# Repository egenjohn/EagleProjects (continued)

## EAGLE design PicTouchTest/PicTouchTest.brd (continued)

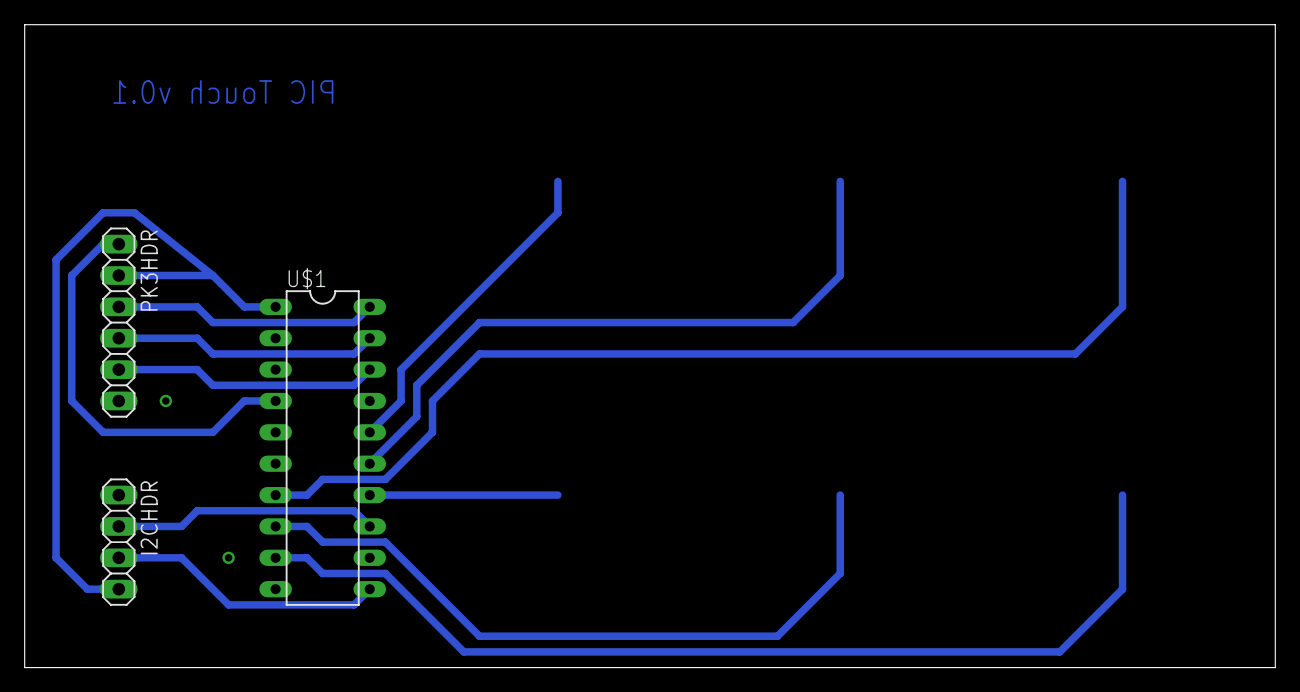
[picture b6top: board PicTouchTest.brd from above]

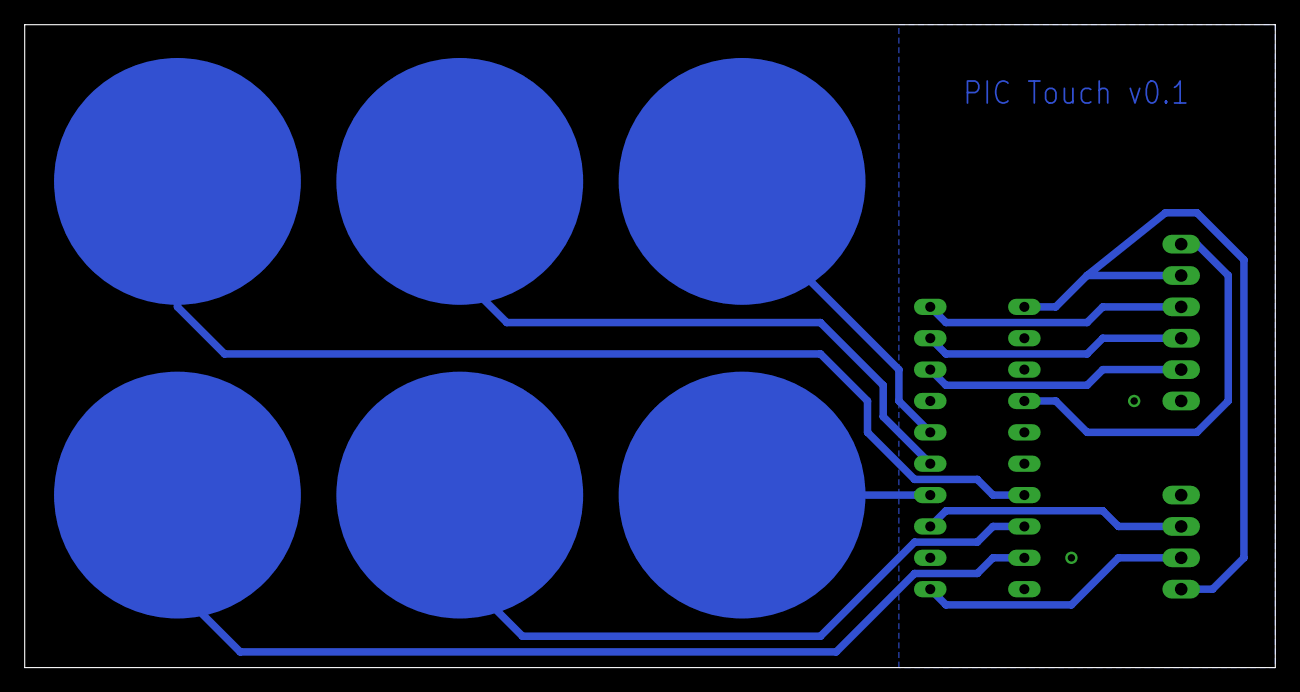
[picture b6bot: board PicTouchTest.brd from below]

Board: 2 copper layers, 101.3 x 52.1 mm, 9 parts (6 on the bottom side), 13 nets.

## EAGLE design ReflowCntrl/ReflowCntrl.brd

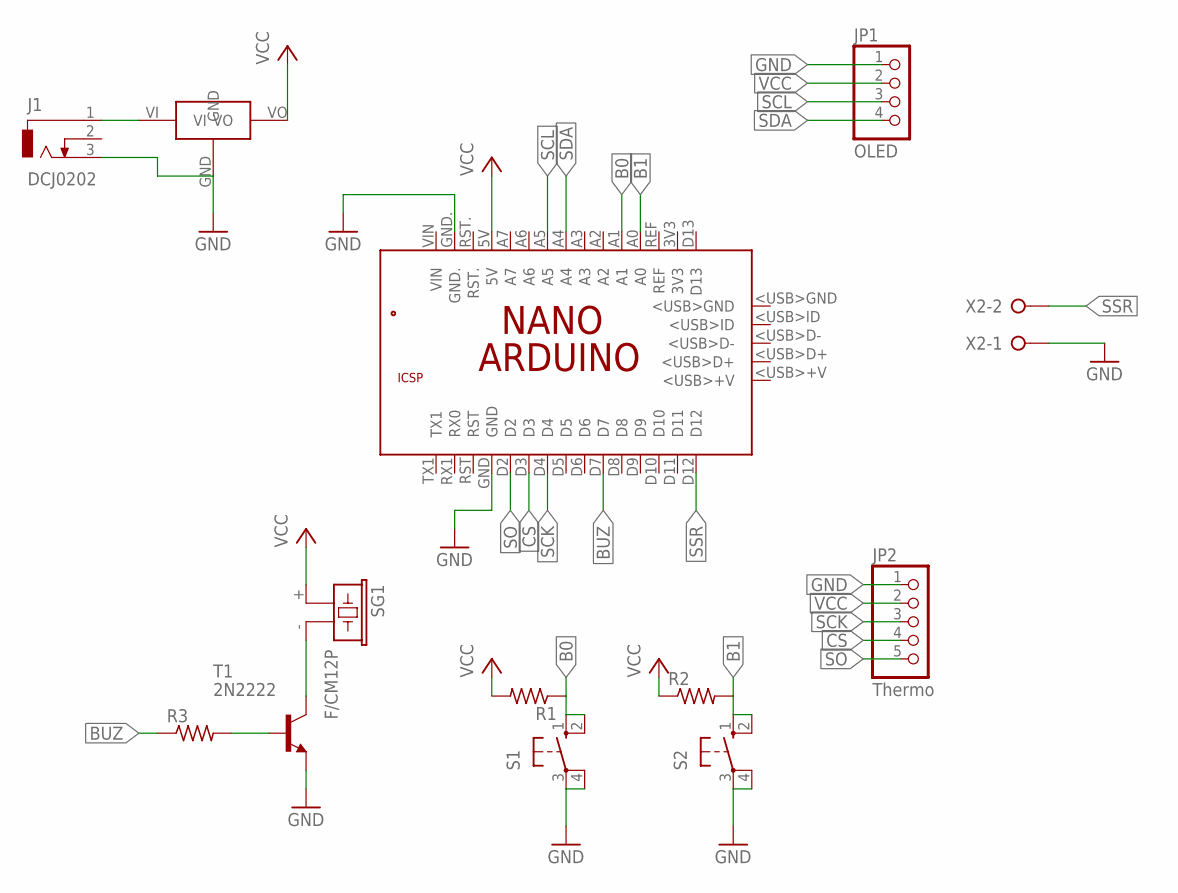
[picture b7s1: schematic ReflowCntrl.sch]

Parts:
J1: DCJ0202
JP1: OLED; 1X04
JP2: Thermo; 1X05
PCB1: ARDUINO_NANO
R1, R2, R3: R-US_0207/10; 0207/10
S1, S2: 10-XX; B3F-10XX
SG1: F/CM12P
T1: 2N2222; TO92-EBC-OVAL
U$1: 7805-TO220V; TO220AV
X2: W237-02P; W237-132

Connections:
B0: PCB1.A1, R1.1, S1.1 (S), S1.2 (S1)
B1: PCB1.A0, R2.2, S2.1 (S), S2.2 (S1)
BUZ: PCB1.D7, R3.1
CS: JP2.4, PCB1.D3
GND: J1.3, JP1.1, JP2.1, PCB1.GND, PCB1.GND., S1.3, S1.4 (P1), S2.3, S2.4 (P1), T1.E, U$1.GND, X2.1
unnamed: SG1.- (2), T1.C
unnamed: R3.2, T1.B
unnamed: J1.1, U$1.VI
SCK: JP2.3, PCB1.D4
SCL: JP1.3, PCB1.A5
SDA: JP1.4, PCB1.A4
SO: JP2.5, PCB1.D2
SSR: PCB1.D12, X2.2
VCC: JP1.2, JP2.2, PCB1.5V, R1.2, R2.1, SG1.+ (1), U$1.VO

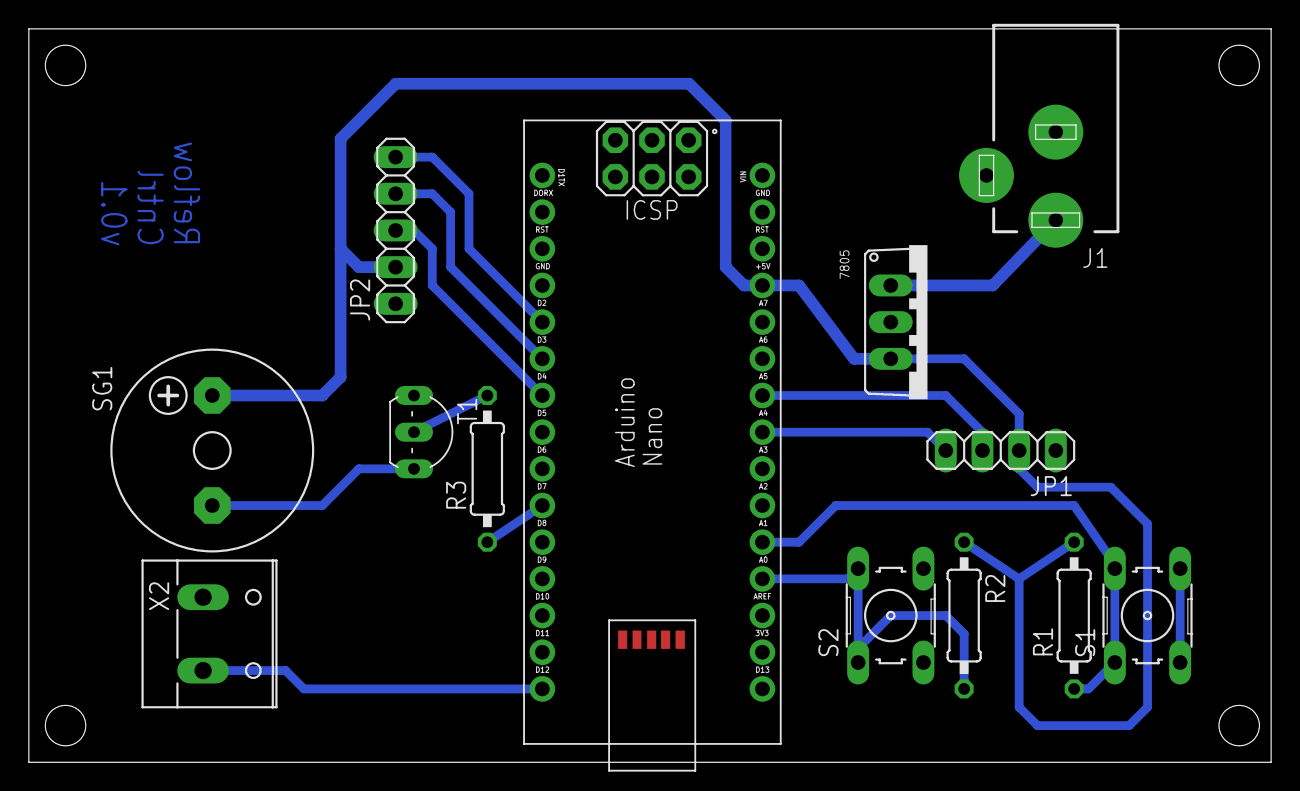
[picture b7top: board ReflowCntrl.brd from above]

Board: 2 copper layers, 86.0 x 50.8 mm, 13 parts (0 on the bottom side), 14 nets.

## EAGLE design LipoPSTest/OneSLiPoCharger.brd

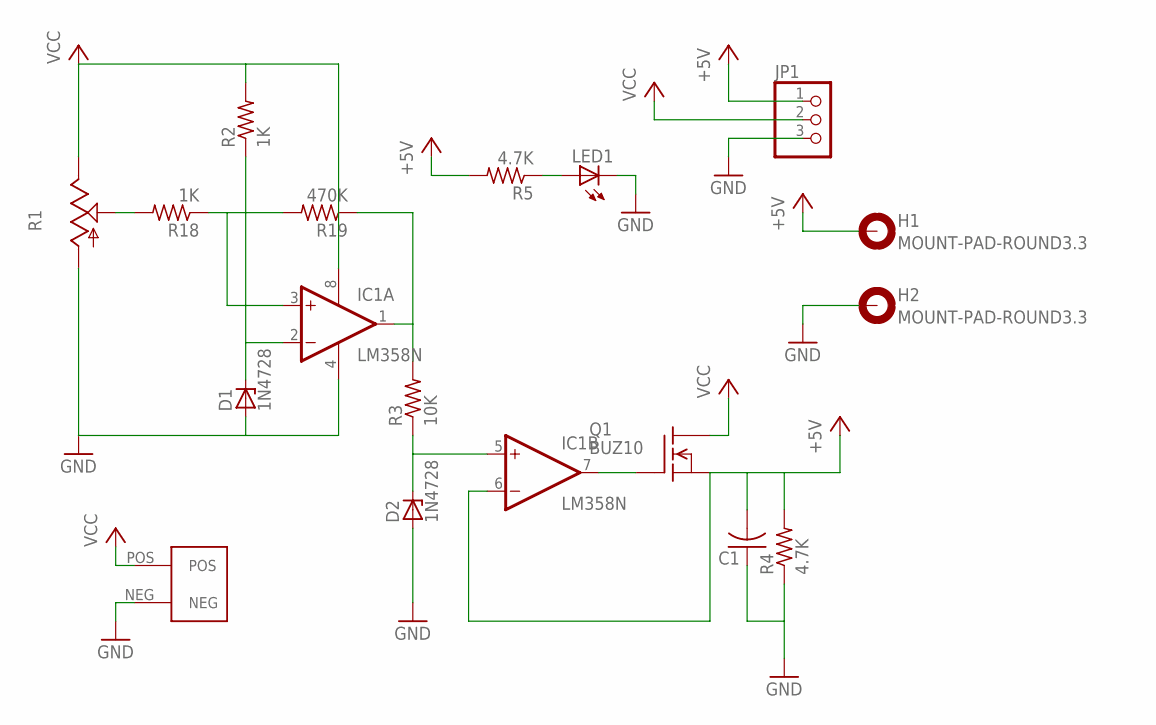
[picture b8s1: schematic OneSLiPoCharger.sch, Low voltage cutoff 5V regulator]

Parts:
C1: C-US025-025X050; C025-025X050
D1, D2: 1N4728; DO41Z10
H1, H2: MOUNT-PAD-ROUND3.3; 3,3-PAD
IC1: LM358N; DIL08
JP1: PINHD-1X3; 1X03
LED1: LED3MM
Q1: BUZ10; TO220
R1: TRIM_US-B25P; B25P
R2, R18: 1K; 0207/10
R3: 10K; 0207/10
R4, R5: 4.7K; 0207/10
R19: 470K; 0207/10
U$3: XT60

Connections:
+5V: C1.2, H1.B3,3, IC1.6 (-IN), JP1.1, Q1.3 (S), R4.2, R5.2
GND: C1.1, D1.A, D2.A, H2.B3,3, IC1.4 (V-), JP1.3, LED1.K (C), R1.A, R4.1, U$3.NEG
unnamed: R1.S, R18.2
unnamed: D2.C, IC1.5 (+IN), R3.1
unnamed: D1.C, IC1.2 (-IN), R2.1
unnamed: IC1.1 (OUT), R3.2, R19.1
unnamed: IC1.7 (OUT), Q1.1 (G)
unnamed: LED1.A, R5.1
unnamed: IC1.3 (+IN), R18.1, R19.2
VCC: IC1.8 (V+), JP1.2, Q1.2 (D), R1.E, R2.2, U$3.POS

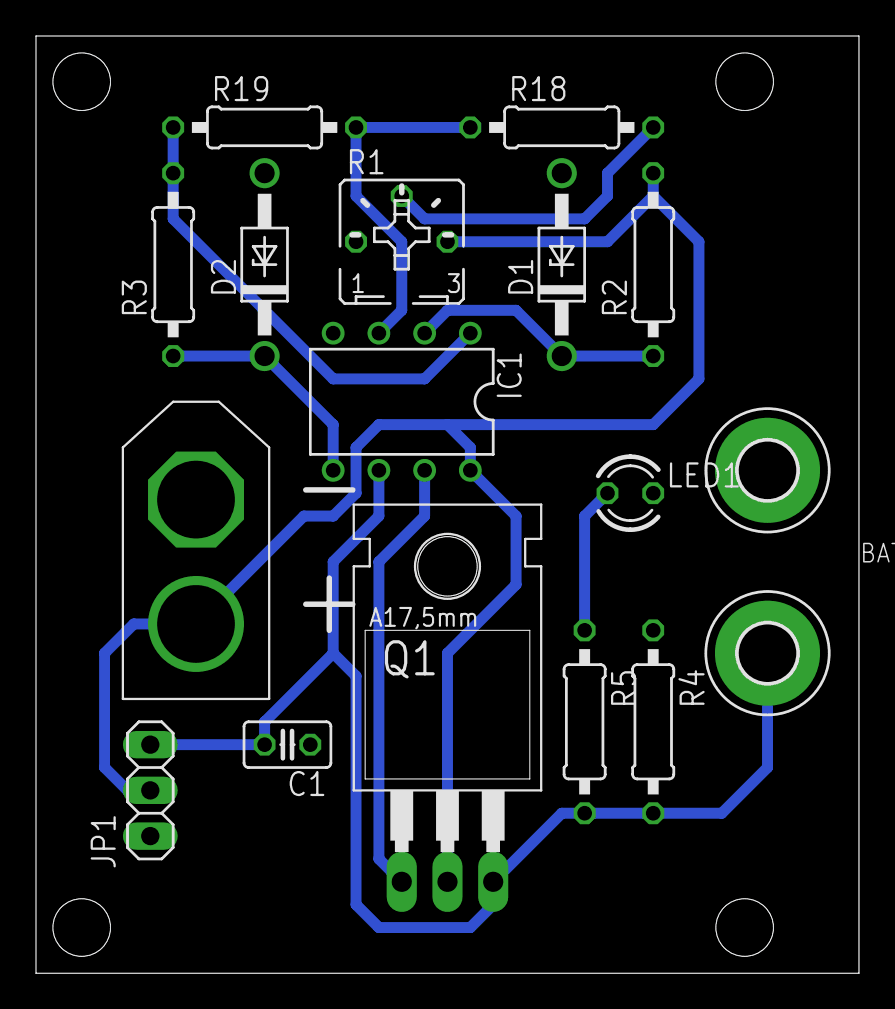
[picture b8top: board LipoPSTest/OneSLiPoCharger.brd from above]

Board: 2 copper layers, 45.7 x 52.1 mm, 18 parts (0 on the bottom side), 10 nets.

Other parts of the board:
DRILEGEND: DRILEGEND

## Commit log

2017-01-05 Initial commit of existing Eagle projects
2017-01-06 Add a xcf file for a tranparency with resist mask and solder mask.
2017-03-24 New project for ATMega328 controlled dual ULN2003 driver.
2017-03-27 Add mounting holes.
2017-03-27 Add a gimp file for transparencies.
2017-05-02 New project for a 1S lipo charger.
2017-05-02 Add XT60 to schematic
2017-05-03 Start laying out the board
2017-05-03 Add all charger circuits
2017-05-04 Schematic update.
2017-05-04 Initial board layout
2017-05-04 Export initial PNGs for masks
2017-05-04 Pull in updates to Picoblade library
2017-05-04 Add a header for a voltmeter module.
2017-05-04 Updated pngs with addition of voltmeter header.
2017-05-05 Create mask transparency image
2017-05-05 Rotate and space the masks a little better.
2017-05-08 Widen isolation. Add ground traces to MCP groups to account for lack of gnd pour. Reduce board width.
2017-05-08 Prep board for OSHPark. Fix feedback on voltage regulator opamp.
2017-05-09 Fix miswired input on first opamp. Add a positive feedback volage divider for some hysteresis.
2017-05-09 Update mask images for recent changes.
2017-05-09 Add serial header to Dual Stepper Controller. Add a new project for a ESP breakout board.
2017-05-09 Move board outline to document layer.
2017-05-09 Add mask images for dual stepper controller.
2017-05-12 Rotate smoothing cap to allow for horizontal electrolitic if needed.
2017-05-12 Fix negative etch mask.
2017-05-13 Add lipo charger test circuits
2017-05-16 New project for MP1584 based lipo charger.
2017-05-16 Add a voltage divider on opamp output to drop voltage for the mp1584 enable pin.
2017-05-17 Clean up addition of the buck module.
2017-05-18 Move the buck module away from the XT60 connector for a bit more clearance.
2017-05-23 Fix some traces to improve etching results
2017-05-24 Initial pass at a case bottom.
2017-06-06 New project for a reflow oven controller.
2017-06-06 Fix swapped VCC and GND pins on OLED. Resized board a bit.
2017-06-06 Add board title text.
2017-06-07 Changed dimension boundry in Arduino Nano library to be tPlace instead to allow gnd plane to flow properly.
2017-06-07 Change SSR terminal to Wago part.
2017-06-07 Change resistors to 0207/10 package
2017-06-07 Move the DC jack so the 7805 can lay flat.
2017-06-08 Add etching images
2017-06-30 Add new project to play with pic capacitive touch support.
2017-06-30 Increase the touch button size to 20mm diameter.
2017-07-06 Nixie power supply test.
2017-07-08 Swap some components.
2017-07-12 Rewire the threshold pin on the 555. Fix some ERC errors.
2017-07-28 Add a nixie clock display project.
2017-07-28 Flip the connection headers.
2017-07-31 Spread out the tubes more. Fix up some traces. Add ground pours.
2017-08-01 Fix up spacing. Change mounting holes to vias.
2017-08-02 Gerbers added for first fab run.
2017-09-17 Add ESP based nixie clock controller.
2017-09-17 Fix cross traces on last digit.
2017-09-17 Add a Wemos based nixie controller project
2017-09-17 Add a 1S charger variant with both picoblade and JST-PH connectors
2017-09-17 Bunch of random updated
2017-09-22 Fix LM317 wiring and add hex inverter.
2018-08-15 New PIC LED display proejct.
2018-08-19 Add a voltage regulator.
2018-08-20 Change power input to padded holes.
2018-08-21 Add a programming header. Moved I2C connector. Changed power connector to 2 pin header. Updated label to v0.2.
2018-08-24 Add NPN transistors for LED cathodes. Add pull ups for I2C lines.
2018-08-24 Updated png to v0.3
2018-08-30 Change ICSP header to standard pin header. Add the ICSP resistor.
2018-08-30 Fixed an overlapping trace.
